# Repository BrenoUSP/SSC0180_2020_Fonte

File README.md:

# Fonte de Tensão
  Projeto de uma fonte de tensão ajustável de 3 a 12 Volts com capacidade de 100 mA, desenvolvido pelo aluno Breno Lívio Silva de Almeida (número USP 10276675).

## Objetivo
  Irá se partir da tensão da tomada (220V ou 127V) que vai ter que ser transformada de 127V/220V em Corrente Alternada (C.A.) em uma tensão adequada para alimentar nosso circuito. Isto é, de 3V-12V em Corrente Contínua (C.C.).

## Desenvolvimento do trabalho

### Componentes
|Nome|Quantidade|Especificações|Explicações|Preço Unitário|
|---|---|---|---|---|
| **Fonte de alimentação** |**1**| **Energia da tomada**| Fonte de energia 127V | ----------- | 
| **Interruptor** |**1**| **250 V e 3 A**| Apenas para ligar e desligar o circuito | [R$28,89](https://produto.mercadolivre.com.br/MLB-1300399738-boto-chave-gangorra-mini-interruptor-liga-desliga-on-off-10x15mm-kcd13-101-3a-250v-arduino-_JM) | 
|**Transformador**|**1**| **bivolt, 15 V e 500 mA**  | Esse transformador foi escolhido visando garantir  uma margem de erro confortável para quedas de tensão nos componentes, além de ser bivolt, podendo lidar com 127V/220V|[R$44,89](https://produto.mercadolivre.com.br/MLB-1305497792-transformador-1515v-2a-trafo-bivolt-_JM) |
|**Ponte Retificadora**|**1**| **1000 V e 2 A** | Responsável por fazer a conversão correta de C.A. para C.C. | [R$3,07](https://produto.mercadolivre.com.br/MLB-1151520283-ponte-retificadora-2w10-2a-1000v-lote-com-10-pecas-_JM)|
|**Capacitor**|**1**| **330 μf/35 V** | Usado para estabilização da tensão do circuito, armazenando energia. O valor se chegou demonstrado pelos cálculos que vão ser explicados em seguida |[R$2,62](https://produto.mercadolivre.com.br/MLB-1475685583-20x-capacitor-eletrolitico-330uf35v-smd-105-10x102mm-_JM)|
|**Diodo Zener**|**1**| **13 V - 0,5 W** | Regula a tensão a 13 V |[R$0,32](https://produto.mercadolivre.com.br/MLB-1395521239-diodo-zener-13v-05w-1n5243-lote-de-100-pecas-_JM)|
|**Transistor**|**1**| **2N2222A ¹** | Atenua a corrente e a tensão. Corrente máxima no coletor de 0.8 mA e tensão máxima do coletor 75 V, mais que o suficiente para trabalhar com 25 V de entrada  |[R$1,05](https://produto.mercadolivre.com.br/MLB-1222136291-20-pecas-transistor-npn-2n2222a-_JM) |
|**Resistência**|**2**| **5,6K Ω** | R1 utilizado para limitar a tensão no zener de modo que está fique na faixa de 13V e o R3 se adapta ao potenciômetro mantendo a tensão de 3V a 12V  |[R$1,08](https://produto.mercadolivre.com.br/MLB-1388075980-50un-resistor-1w-de-potencia-escolha-1-valor-ohmico-na-lista-_JM) 
|**Potenciômetro**|**1**| **10k Ω**  | Mantém a tensão da fonte entre 3 V e 12 V | [R$2,8](https://produto.mercadolivre.com.br/MLB-882483201-10x-potencimetro-10k-linear-com-eixo-l20-estriado-_JM)|

|**Preço total (com o frete)**|
|---|
|R$84,72|

### Cálculos

  Foi necessário realizar contas específicas se utilizando dos princípios da eletrônica para se obter os valores usados pelos componentes para se ter um circuito funcional. Primeiro deve-se calcular a tensão de pico primário, considerando a tensão de entrada sendo a fonte de alimentação de 127 V:

  <div align="center">

</div>

  Em seguida calcula-se a tensão de pico secundário, levando-se o conta o ripple, na eletrônica é um valor residual e periódico obtido de uma fonte de tensão que, por sua vez, é alimentada por uma corrente alternada. Para isso busca-se um ripple de 10% ² da tensão de saída esperada de 25 V, ou seja, 2,5 V. Além disso, considera-se a tensão de um diodo de silício, em 0,65 V:

  <div align="center">

</div>

  O período é dado por:

  <div align="center">

</div>

  Com o período, encontra-se o tempo de carga:
  
  <div align="center">

</div>

  Por fim, é possível encontrar a fórmula da capacitância ³, o que auxiliou a escolher um valor adequado para o **capacitor** de 330 µF, por ser acima do encontrado e por ser um valor comercial:
  
  <div align="center">

</div>

### Vídeo-tutorial

  O vídeo a seguir descreve exatamente como o projeto foi criado, esclarecendo melhor como utilizar as ferramentas e softwares em questão.

### Simulador Falstad

<div align="center">

</div>

  Falstad é um applet originalmente desenvolvido em Java, agora numa versão Javascript, feito para fazer simulações com circuitos. Você pode encontrar o repositório no GitHub [aqui](https://github.com/pfalstad/circuitjs1/).

  A simulação desse trabalho: [Link da simulação](http://tinyurl.com/y7hmerds)

### EAGLE

  Para o desenvolvimento de um esquemático e da PCB do circuito, foi utilizado do software EAGLE, que foi ensinado pelo professor sobre suas capacidades e instruções importantes para o desenvolvimento eficaz de circuitos como os esperados na disciplina.
  
#### Esquemático

  O projeto esquemático no EAGLE é análogo a uma "planta" de um circuito. Nele são ilustrados os componentes, valores e suas conexões no circuito.

<div align="center">

</div>

#### PCB

  O PCB é uma placa dedicada a expressar as conexões de um determinado circuito, auxiliando numa instalação mais precisa e compacta de um circuito. Nota-se que para impressão desse circuito, a imagem deve estar como espelhada, sendo assim possível transcever o circuito diretamente na placa com alguma caneta ou análogo. Além disso, é necessário esclarecer que para um circuito em escala real, o transformador provavelmente ficaria fora da placa PCB.

<div align="center">

</div>

### Bibliografia

¹ [Datasheet do transistor usado](https://www.onsemi.com/pub/Collateral/P2N2222A-D.PDF)

² [Valor adequado para o ripple](https://www.google.com/url?sa=t&rct=j&q=&esrc=s&source=web&cd=&cad=rja&uact=8&ved=2ahUKEwj-1ueMl8vqAhXzGrkGHRRABXgQFjAEegQIAhAB&url=https%3A%2F%2Feasa.com%2FDesktopModules%2FEasyDNNNews%2FDocumentDownload.ashx%3Fportalid%3D0%26moduleid%3D2293%26articleid%3D1857%26documentid%3D876&usg=AOvVaw0ZTCSKv9-sH4zlEOMl2173)

³ [Fórmula da capacitância mínima, da Texas Instruments](https://www.ti.com/lit/an/slta055/slta055.pdf)

Trabalho proposto pelo professor Eduardo Simões para a matéria de Eletrônica do Curso de Bacharelado em Ciências de Computação do Instituto de Ciências Matemáticas e de Computação (ICMC-USP).

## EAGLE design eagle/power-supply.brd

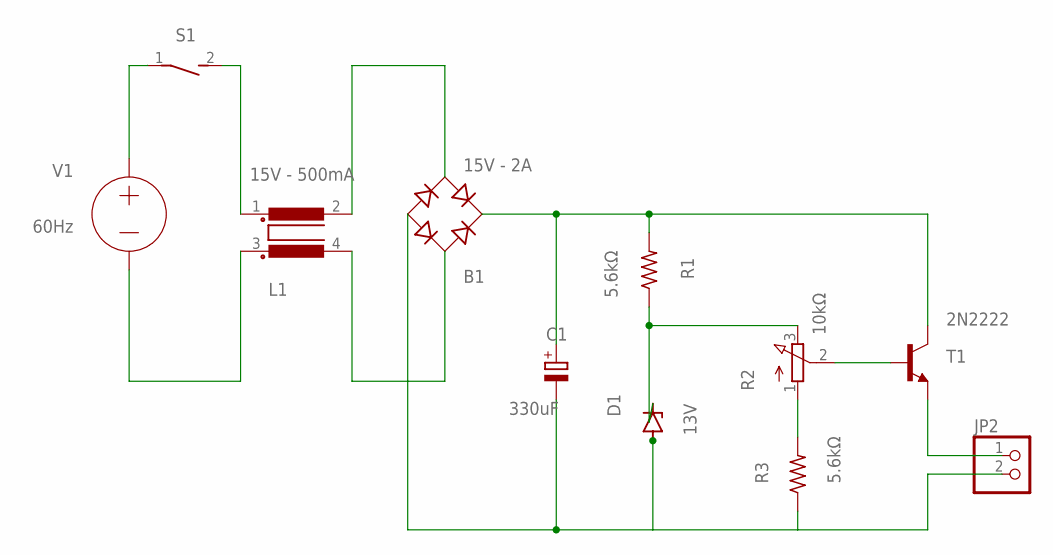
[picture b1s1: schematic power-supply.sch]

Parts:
B1: 15V - 2A; RB1A
C1: 330uF; E3,5-10
D1: 13V; DO41Z10
JP2: PINHD-1X2; 1X02
L1: 15V - 500mA; B2
R1, R3: 5.6kΩ; 0309/12
R2: 10kΩ; 3RP/1610N
S1: DS01E; DS-01
T1: 2N2222; TO18

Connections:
unnamed: R2.1 (A), R3.2
unnamed: B1.AC2, L1.2
unnamed: B1.AC1, L1.4
unnamed: D1.C, R1.1, R2.3 (E)
unnamed: B1.+, C1.+, R1.2, T1.3 (C)
unnamed: B1.-, C1.-, D1.A, JP2.2, R3.1
unnamed: JP2.1, T1.1 (E)
unnamed: L1.1, S1.2
unnamed: R2.2 (S), T1.2 (B)

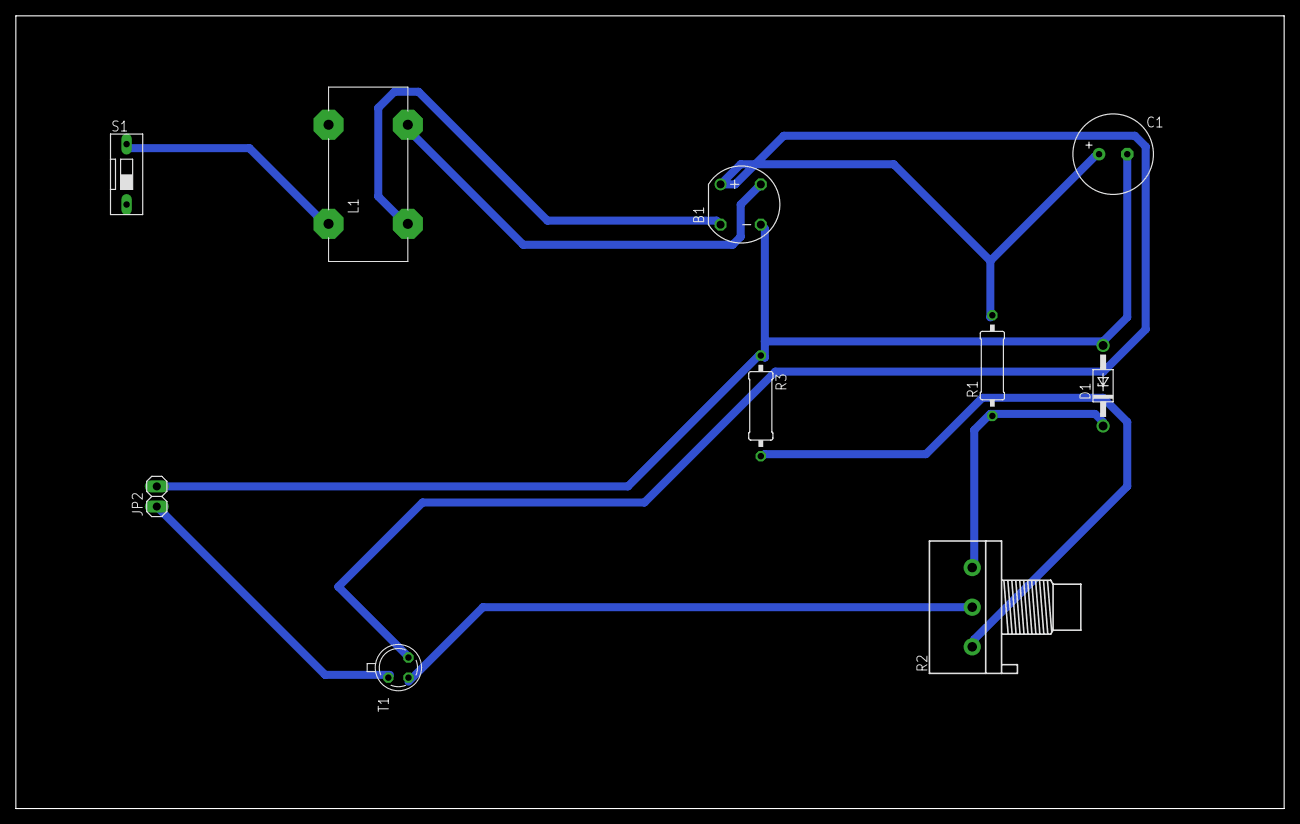
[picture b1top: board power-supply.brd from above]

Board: 2 copper layers, 160.0 x 100.0 mm, 10 parts (0 on the bottom side), 9 nets.

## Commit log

2020-07-09 Preparando estrutura do README
2020-07-09 new images
2020-07-09 Update README.md
    Explicação dos cálculos
2020-07-13 Preços adicionados
2020-07-13 Adicionando bibliografia
2020-07-13 Falstad circuit animation gif
2020-07-13 Correção de símbolos e adição de mais links para a bibliografia
2020-07-13 Informações sobre esquemático e PCB
2020-07-13 Imagens esquemático e PCB
2020-07-13 Erros textuais
2020-07-13 Arquivos do EAGLE
2020-07-14 Vídeo adicionado
2020-07-14 Correção nome arquivo thumbnail
2020-07-14 Arquivo de thumbnail do vídeo
2020-07-14 new thumbnail
2020-07-14 Correção de erros no EAGLE
2020-07-14 Imagem da PCB atualizado com fios corretos
2020-07-14 Imagem do PCB atualizado
2020-07-14 Atualizado com observação do professor
